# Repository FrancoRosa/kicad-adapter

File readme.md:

# kicad adapter
> random scripts to generarte kicad files from pnez files for test applications

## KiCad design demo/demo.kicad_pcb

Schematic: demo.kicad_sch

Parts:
INV0, INV1, INV2, INV3, INV4, INV5, INV6, INV7, INV8, INV9, INV10, INV11, INV12, INV13, INV14, INV15, INV16, INV17, INV18, INV19, INV20, INV21, INV22, INV23, INV24, INV25, INV26, INV27, INV28, INV29, INV30, INV31, INV32, INV33, INV34, INV35, INV36, INV37, INV38, INV39: TestPoint; TestPoint_Pad_D1.0mm
PILE0, PILE1, PILE2, PILE3, PILE4, PILE5, PILE6, PILE7, PILE8, PILE9, PILE10, PILE11, PILE12, PILE13, PILE14, PILE15, PILE16, PILE17, PILE18, PILE19, PILE20, PILE21, PILE22, PILE23, PILE24, PILE25, PILE26, PILE27, PILE28, PILE29, PILE30, PILE31, PILE32, PILE33, PILE34, PILE35, PILE36, PILE37, PILE38, PILE39, PILE40, PILE41, PILE42, PILE43, PILE44, PILE45, PILE46, PILE47, PILE48, PILE49, PILE50, PILE51, PILE52, PILE53, PILE54, PILE55, PILE56, PILE57, PILE58, PILE59, PILE60, PILE61, PILE62, PILE63, PILE64, PILE65, PILE66, PILE67, PILE68, PILE69, PILE70, PILE71, PILE72, PILE73, PILE74, PILE75, PILE76, PILE77, PILE78, PILE79, PILE80, PILE81, PILE82, PILE83, PILE84, PILE85, PILE86, PILE87, PILE88, PILE89, PILE90, PILE91, PILE92, PILE93, PILE94, PILE95, PILE96, PILE97, PILE98, PILE99, PILE100, PILE101, PILE102, PILE103, PILE104, PILE105, PILE106, PILE107, PILE108, PILE109, PILE110, PILE111, PILE112, PILE113, PILE114, PILE115, PILE116, PILE117, PILE118, PILE119, PILE120, PILE121, PILE122, PILE123, PILE124, PILE125, PILE126, PILE127, PILE128, PILE129, PILE130, PILE131, PILE132, PILE133, PILE134, PILE135, PILE136, PILE137, PILE138, PILE139, PILE140, PILE141, PILE142, PILE143, PILE144, PILE145, PILE146, PILE147, PILE148, PILE149, PILE150, PILE151, PILE152, PILE153, PILE154, PILE155, PILE156, PILE157, PILE158, PILE159, PILE160, PILE161, PILE162, PILE163, PILE164, PILE165, PILE166, PILE167, PILE168, PILE169, PILE170, PILE171, PILE172, PILE173, PILE174, PILE175, PILE176, PILE177, PILE178, PILE179, PILE180, PILE181, PILE182, PILE183, PILE184, PILE185, PILE186, PILE187, PILE188, PILE189, PILE190, PILE191, PILE192, PILE193, PILE194, PILE195, PILE196, PILE197, PILE198, PILE199, PILE200, PILE201, PILE202, PILE203, PILE204, PILE205, PILE206, PILE207, PILE208, PILE209, PILE210, PILE211, PILE212, PILE213, PILE214, PILE215, PILE216, PILE217, PILE218, PILE219, PILE220, PILE221, PILE222, PILE223, PILE224, PILE225, PILE226, PILE227, PILE228, PILE229, PILE230, PILE231, PILE232, PILE233, PILE234, PILE235, PILE236, PILE237, PILE238, PILE239, PILE240, PILE241, PILE242, PILE243, PILE244, PILE245, PILE246, PILE247, PILE248, PILE249, PILE250, PILE251, PILE252, PILE253, PILE254, PILE255, PILE256, PILE257, PILE258, PILE259, PILE260, PILE261, PILE262, PILE263, PILE264, PILE265, PILE266, PILE267, PILE268, PILE269, PILE270, PILE271, PILE272, PILE273, PILE274, PILE275, PILE276, PILE277, PILE278, PILE279, PILE280, PILE281, PILE282, PILE283, PILE284, PILE285, PILE286, PILE287, PILE288, PILE289, PILE290, PILE291, PILE292, PILE293, PILE294, PILE295, PILE296, PILE297, PILE298, PILE299, PILE300, PILE301, PILE302, PILE303, PILE304, PILE305, PILE306, PILE307, PILE308, PILE309, PILE310, PILE311, PILE312, PILE313, PILE314, PILE315, PILE316, PILE317, PILE318, PILE319, PILE320, PILE321, PILE322, PILE323, PILE324, PILE325, PILE326, PILE327, PILE328, PILE329, PILE330, PILE331, PILE332, PILE333, PILE334, PILE335, PILE336, PILE337, PILE338, PILE339, PILE340, PILE341, PILE342, PILE343, PILE344, PILE345, PILE346, PILE347, PILE348, PILE349, PILE350, PILE351, PILE352, PILE353, PILE354, PILE355, PILE356, PILE357, PILE358, PILE359, PILE360, PILE361, PILE362, PILE363, PILE364, PILE365, PILE366, PILE367, PILE368, PILE369, PILE370, PILE371, PILE372, PILE373, PILE374, PILE375, PILE376, PILE377, PILE378, PILE379, PILE380, PILE381, PILE382, PILE383, PILE384, PILE385, PILE386, PILE387, PILE388, PILE389, PILE390, PILE391, PILE392, PILE393, PILE394, PILE395, PILE396, PILE397, PILE398, PILE399, PILE400, PILE401, PILE402, PILE403, PILE404, PILE405, PILE406, PILE407, PILE408, PILE409, PILE410, PILE411, PILE412, PILE413, PILE414, PILE415, PILE416, PILE417, PILE418, PILE419, PILE420, PILE421, PILE422, PILE423, PILE424, PILE425, PILE426, PILE427, PILE428, PILE429, PILE430, PILE431, PILE432, PILE433, PILE434, PILE435, PILE436, PILE437, PILE438, PILE439, PILE440, PILE441, PILE442, PILE443, PILE444, PILE445, PILE446, PILE447, PILE448, PILE449, PILE450, PILE451, PILE452, PILE453, PILE454, PILE455, PILE456, PILE457, PILE458, PILE459, PILE460, PILE461, PILE462, PILE463, PILE464, PILE465, PILE466, PILE467, PILE468, PILE469, PILE470, PILE471, PILE472, PILE473, PILE474, PILE475, PILE476, PILE477, PILE478, PILE479, PILE480, PILE481, PILE482, PILE483, PILE484, PILE485, PILE486, PILE487, PILE488, PILE489, PILE490, PILE491, PILE492, PILE493, PILE494, PILE495, PILE496, PILE497, PILE498, PILE499, PILE500, PILE501, PILE502, PILE503, PILE504, PILE505, PILE506, PILE507, PILE508, PILE509, PILE510, PILE511, PILE512, PILE513, PILE514, PILE515, PILE516, PILE517, PILE518, PILE519, PILE520, PILE521, PILE522, PILE523, PILE524, PILE525, PILE526, PILE527, PILE528, PILE529, PILE530, PILE531, PILE532, PILE533, PILE534, PILE535, PILE536, PILE537, PILE538, PILE539, PILE540, PILE541, PILE542, PILE543, PILE544, PILE545, PILE546, PILE547, PILE548, PILE549, PILE550, PILE551, PILE552, PILE553, PILE554, PILE555, PILE556, PILE557, PILE558, PILE559, PILE560, PILE561, PILE562, PILE563, PILE564, PILE565, PILE566, PILE567, PILE568, PILE569, PILE570, PILE571, PILE572, PILE573, PILE574, PILE575, PILE576, PILE577, PILE578, PILE579, PILE580, PILE581, PILE582, PILE583, PILE584, PILE585, PILE586, PILE587, PILE588, PILE589, PILE590, PILE591, PILE592, PILE593, PILE594, PILE595, PILE596, PILE597, PILE598, PILE599, PILE600, PILE601, PILE602, PILE603, PILE604, PILE605, PILE606, PILE607, PILE608, PILE609, PILE610, PILE611, PILE612, PILE613, PILE614, PILE615, PILE616, PILE617, PILE618, PILE619, PILE620, PILE621, PILE622, PILE623, PILE624, PILE625, PILE626, PILE627, PILE628, PILE629, PILE630, PILE631, PILE632, PILE633, PILE634, PILE635, PILE636, PILE637, PILE638, PILE639, PILE640, PILE641, PILE642, PILE643, PILE644, PILE645, PILE646, PILE647, PILE648, PILE649, PILE650, PILE651, PILE652, PILE653, PILE654, PILE655, PILE656, PILE657, PILE658, PILE659, PILE660, PILE661, PILE662, PILE663, PILE664, PILE665, PILE666, PILE667, PILE668, PILE669, PILE670, PILE671, PILE672, PILE673, PILE674, PILE675, PILE676, PILE677, PILE678, PILE679, PILE680, PILE681, PILE682, PILE683, PILE684, PILE685, PILE686, PILE687, PILE688, PILE689, PILE690, PILE691, PILE692, PILE693, PILE694, PILE695, PILE696, PILE697, PILE698, PILE699, PILE700, PILE701, PILE702, PILE703, PILE704, PILE705, PILE706, PILE707, PILE708, PILE709, PILE710, PILE711, PILE712, PILE713, PILE714, PILE715, PILE716, PILE717, PILE718, PILE719, PILE720, PILE721, PILE722, PILE723, PILE724, PILE725, PILE726, PILE727, PILE728, PILE729, PILE730, PILE731, PILE732, PILE733, PILE734, PILE735, PILE736, PILE737, PILE738, PILE739, PILE740, PILE741, PILE742, PILE743, PILE744, PILE745, PILE746, PILE747, PILE748, PILE749, PILE750, PILE751, PILE752, PILE753, PILE754, PILE755, PILE756, PILE757, PILE758, PILE759, PILE760, PILE761, PILE762, PILE763, PILE764, PILE765, PILE766, PILE767, PILE768, PILE769, PILE770, PILE771, PILE772, PILE773, PILE774, PILE775, PILE776, PILE777, PILE778, PILE779, PILE780, PILE781, PILE782, PILE783, PILE784, PILE785, PILE786, PILE787, PILE788, PILE789, PILE790, PILE791, PILE792, PILE793, PILE794, PILE795, PILE796, PILE797, PILE798, PILE799, PILE800, PILE801, PILE802, PILE803, PILE804, PILE805, PILE806, PILE807, PILE808, PILE809, PILE810, PILE811, PILE812, PILE813, PILE814, PILE815, PILE816, PILE817, PILE818, PILE819, PILE820, PILE821, PILE822, PILE823, PILE824, PILE825, PILE826, PILE827, PILE828, PILE829, PILE830, PILE831, PILE832, PILE833, PILE834, PILE835, PILE836, PILE837, PILE838, PILE839, PILE840, PILE841, PILE842, PILE843, PILE844, PILE845, PILE846, PILE847, PILE848, PILE849, PILE850, PILE851, PILE852, PILE853, PILE854, PILE855, PILE856, PILE857, PILE858, PILE859, PILE860, PILE861, PILE862, PILE863, PILE864, PILE865, PILE866, PILE867, PILE868, PILE869, PILE870, PILE871, PILE872, PILE873, PILE874, PILE875, PILE876, PILE877, PILE878, PILE879, PILE880, PILE881, PILE882, PILE883, PILE884, PILE885, PILE886, PILE887, PILE888, PILE889, PILE890, PILE891, PILE892, PILE893, PILE894, PILE895, PILE896, PILE897, PILE898, PILE899, PILE900, PILE901, PILE902, PILE903, PILE904, PILE905, PILE906, PILE907, PILE908, PILE909, PILE910, PILE911, PILE912, PILE913, PILE914, PILE915, PILE916, PILE917, PILE918, PILE919, PILE920, PILE921, PILE922, PILE923, PILE924, PILE925, PILE926, PILE927, PILE928, PILE929, PILE930, PILE931, PILE932, PILE933, PILE934, PILE935, PILE936, PILE937, PILE938, PILE939, PILE940, PILE941, PILE942, PILE943, PILE944, PILE945, PILE946, PILE947, PILE948, PILE949, PILE950, PILE951, PILE952, PILE953, PILE954, PILE955, PILE956, PILE957, PILE958, PILE959, PILE960, PILE961, PILE962, PILE963, PILE964, PILE965, PILE966, PILE967, PILE968, PILE969, PILE970, PILE971, PILE972, PILE973, PILE974, PILE975, PILE976, PILE977, PILE978, PILE979, PILE980, PILE981, PILE982, PILE983, PILE984, PILE985, PILE986, PILE987, PILE988, PILE989, PILE990, PILE991, PILE992, PILE993, PILE994, PILE995, PILE996, PILE997, PILE998, PILE999, PILE1000, PILE1001, PILE1002, PILE1003, PILE1004, PILE1005, PILE1006, PILE1007, PILE1008, PILE1009, PILE1010, PILE1011, PILE1012, PILE1013, PILE1014, PILE1015, PILE1016, PILE1017, PILE1018, PILE1019, PILE1020, PILE1021, PILE1022, PILE1023, PILE1024, PILE1025, PILE1026, PILE1027, PILE1028, PILE1029, PILE1030, PILE1031, PILE1032, PILE1033, PILE1034, PILE1035, PILE1036, PILE1037, PILE1038, PILE1039, PILE1040, PILE1041, PILE1042, PILE1043, PILE1044, PILE1045, PILE1046, PILE1047, PILE1048, PILE1049, PILE1050, PILE1051, PILE1052, PILE1053, PILE1054, PILE1055, PILE1056, PILE1057, PILE1058, PILE1059, PILE1060, PILE1061, PILE1062, PILE1063, PILE1064, PILE1065, PILE1066, PILE1067, PILE1068, PILE1069, PILE1070, PILE1071, PILE1072, PILE1073, PILE1074, PILE1075, PILE1076, PILE1077, PILE1078, PILE1079, PILE1080, PILE1081, PILE1082, PILE1083, PILE1084, PILE1085, PILE1086, PILE1087, PILE1088, PILE1089, PILE1090, PILE1091, PILE1092, PILE1093, PILE1094, PILE1095, PILE1096, PILE1097, PILE1098, PILE1099, PILE1100, PILE1101, PILE1102, PILE1103, PILE1104, PILE1105, PILE1106, PILE1107, PILE1108, PILE1109, PILE1110, PILE1111, PILE1112, PILE1113, PILE1114, PILE1115, PILE1116, PILE1117, PILE1118, PILE1119, PILE1120, PILE1121, PILE1122, PILE1123, PILE1124, PILE1125, PILE1126, PILE1127, PILE1128, PILE1129, PILE1130, PILE1131, PILE1132, PILE1133, PILE1134, PILE1135, PILE1136, PILE1137, PILE1138, PILE1139, PILE1140, PILE1141, PILE1142, PILE1143, PILE1144, PILE1145, PILE1146, PILE1147, PILE1148, PILE1149, PILE1150, PILE1151, PILE1152, PILE1153, PILE1154, PILE1155, PILE1156, PILE1157, PILE1158, PILE1159, PILE1160, PILE1161, PILE1162, PILE1163, PILE1164, PILE1165: TestPoint; TestPoint_Pad_D1.0mm

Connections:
unnamed: INV0.1, INV34.1
unnamed: INV1.1, INV25.1
unnamed: INV2.1, INV24.1
unnamed: INV10.1, INV21.1
unnamed: INV11.1, INV38.1
unnamed: INV12.1, INV39.1
unnamed: INV13.1, INV20.1
unnamed: INV14.1, INV27.1
unnamed: INV15.1, INV28.1
unnamed: INV16.1, INV29.1
unnamed: INV17.1, INV32.1
unnamed: INV18.1, INV31.1
unnamed: INV19.1, INV30.1
unnamed: INV9.1, INV22.1
unnamed: INV4.1, INV23.1
unnamed: INV3.1, INV26.1
unnamed: INV7.1, INV33.1
unnamed: INV6.1, INV35.1
unnamed: INV5.1, INV36.1
unnamed: INV8.1, INV37.1

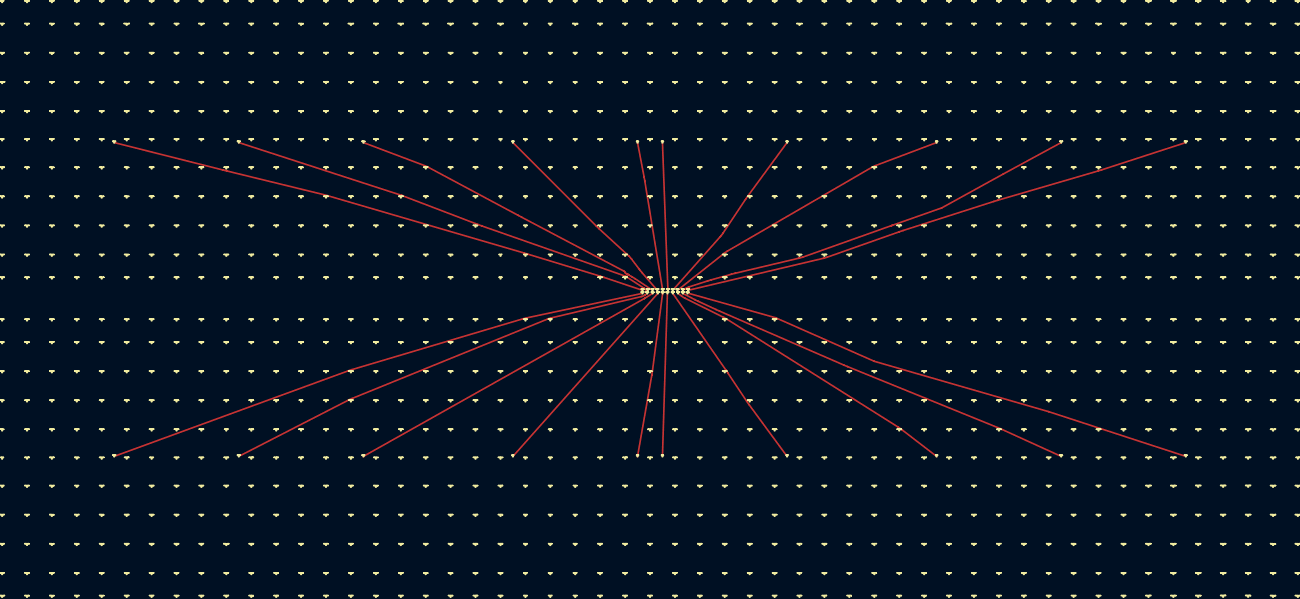
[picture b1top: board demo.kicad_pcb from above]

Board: 2 copper layers, 1206 parts (0 on the bottom side), 20 nets.

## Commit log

2023-08-19 Modify pads
2023-08-19 Get coordinates from pcb
2023-08-20 Add routing scripts
2023-08-20 output to file with identtations
2023-08-20 Add espg code to conversion
2023-08-20 Avoid nested brackets
